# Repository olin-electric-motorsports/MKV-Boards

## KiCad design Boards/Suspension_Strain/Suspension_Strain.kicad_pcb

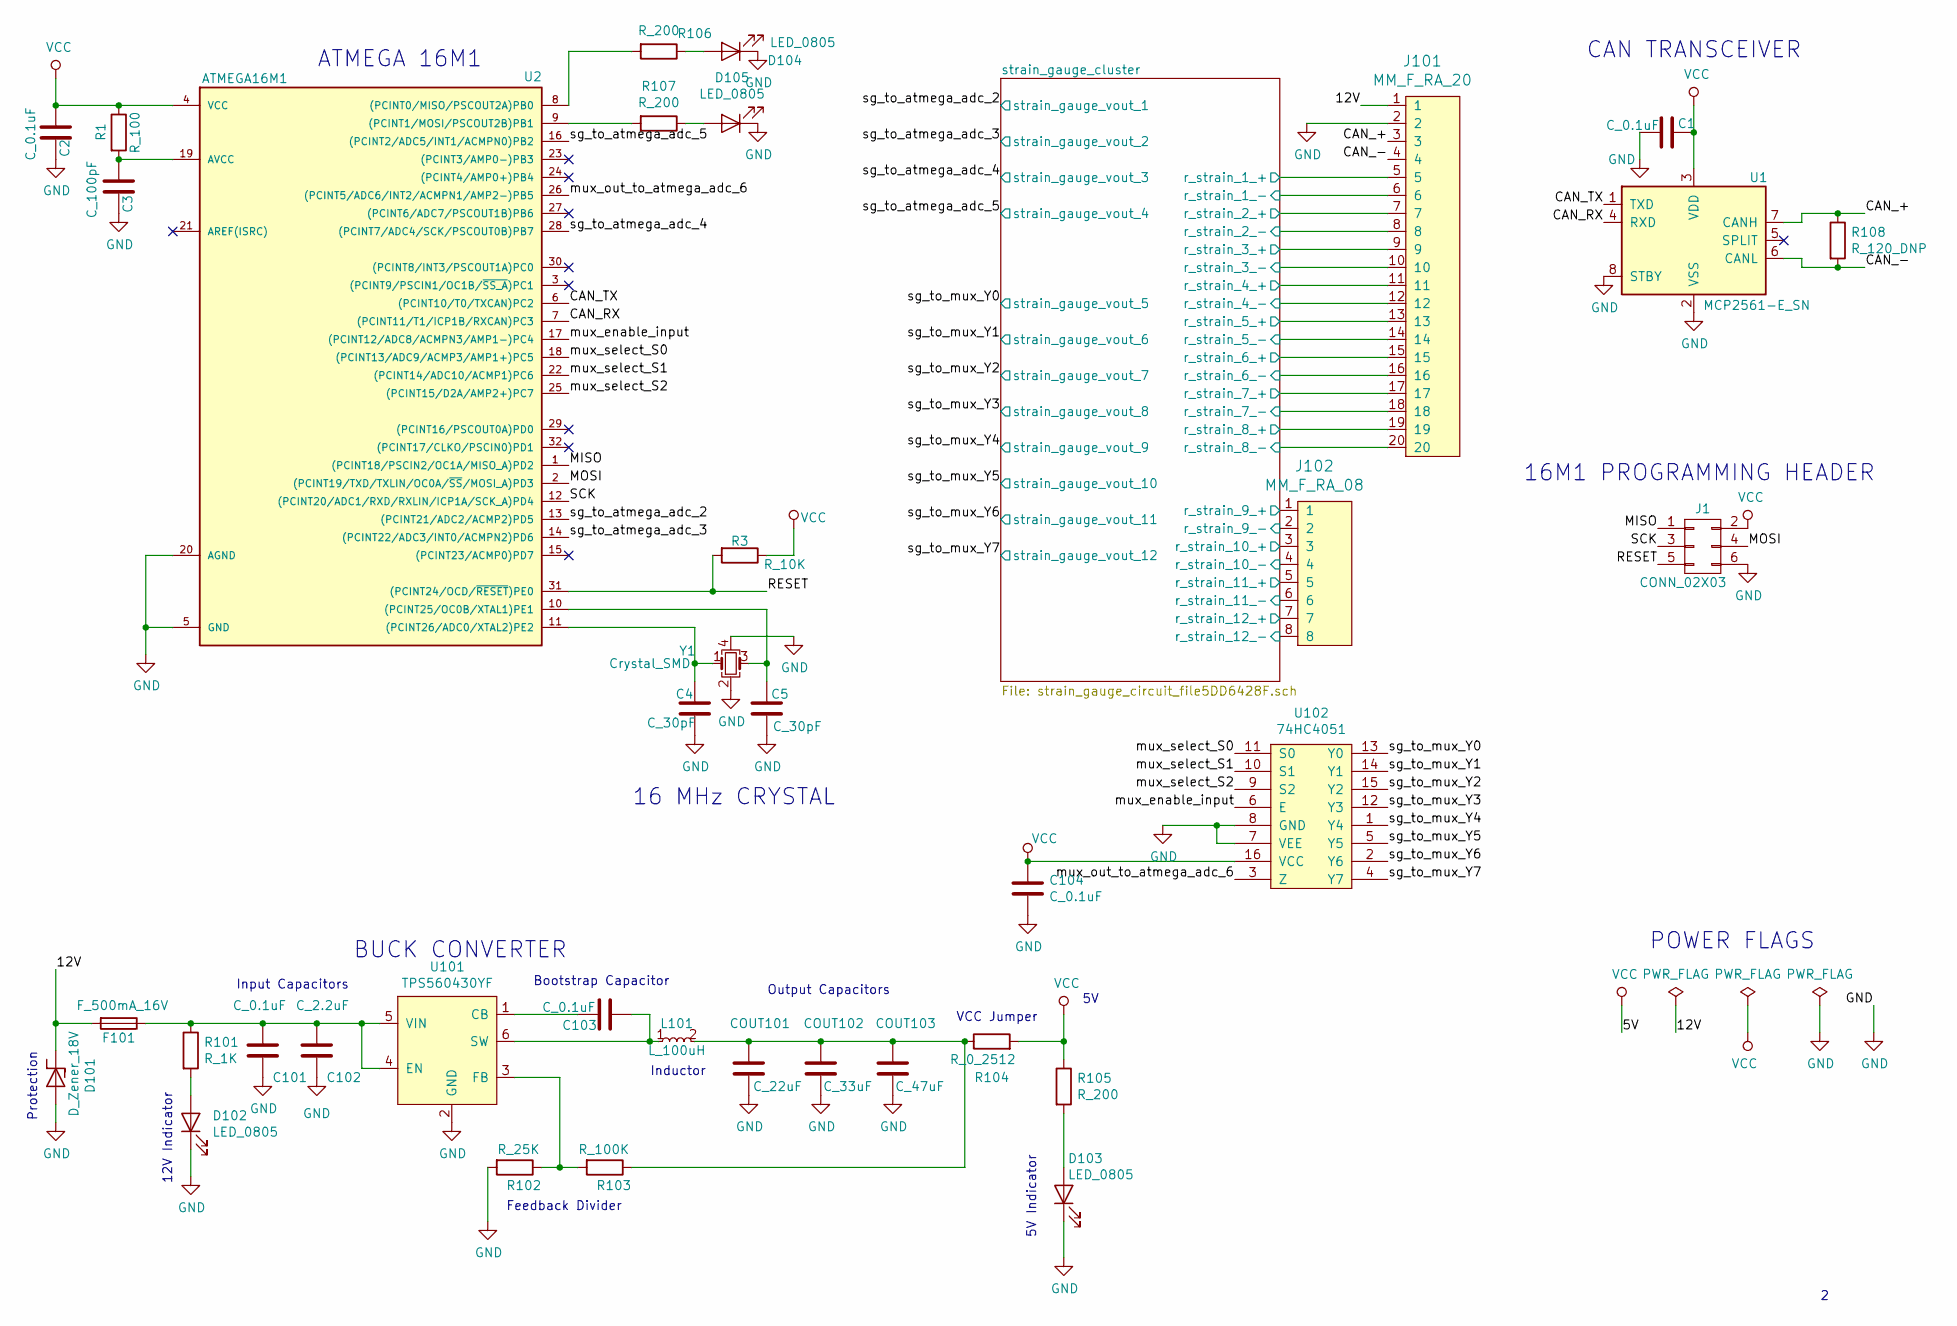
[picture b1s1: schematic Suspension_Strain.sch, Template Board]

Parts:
C1, C2, C101, C103, C104: C_0.1uF; C_0805_OEM; MPN 478-3352-1-ND
C3: C_100pF; C_0805_OEM; MPN 732-7852-1-ND
C4, C5: C_30pF; C_0805_OEM; MPN 1276-1130-1-ND
C102: C_2.2uF; C_0603_1608Metric; MPN 311-1451-1-ND
COUT101: C_22uF; C_1206_OEM; MPN 445-11693-1-ND
COUT102: C_33uF; C_1812_OEM; MPN 445-3924-1-ND
COUT103: C_47uF; C_0805_OEM; MPN 1276-6467-1-ND
D101: D_Zener_18V; DO-214AA; MPN SMBJ5355B-TPMSCT-ND
D102, D103, D104, D105: LED_0805; LED_0805_OEM; MPN 475-1410-1-ND
F101: F_500mA_16V; Fuse_1210; MPN 507-1786-1-ND
J1: CONN_02X03; Pin_Header_Straight_2x03; MPN 609-3234-ND
J101: MM_F_RA_20; micromatch_female_ra_20; MPN 2-338070-0
J102: MM_F_RA_08; micromatch_female_ra_8; MPN 338070-8
L101: L_100uH; L_100uH_OEM; MPN 445-15759-1-ND
R1: R_100; R_0805_OEM; MPN RNCP0805FTD100RCT-ND
R3: R_10K; R_0805_OEM; MPN CRS0805-FX-1002ELFCT-ND
R101: R_1K; R_0805_OEM; MPN RNCP0805FTD1K00CT-ND
R102: R_25K; R_0805_OEM; Digi-key Part Number CPF-A-0805B25KE
R103: R_100K; R_0805_OEM; MPN P100KCCT-ND
R104: R_0_2512; R_2512_OEM; MPN A121322CT-ND
R105, R106, R107: R_200; R_0805_OEM; MPN RMCF0805JT200RCT-ND
R108: R_120_DNP; R_0805_OEM; MPN 667-ERJ-6ENF1200V
U1: MCP2561-E_SN; SOIC-8_3.9x4.9mm_Pitch1.27mm_OEM; MPN MCP2561-E/SN-ND
U2: ATMEGA16M1; TQFP-32_7x7mm_Pitch0.8mm; MPN ATMEGA16M1-AU-ND
U101: TPS560430YF; SOT-23-6_Handsoldering; MPN TPS560430YFDBVR
U102: 74HC4051; TSSOP-16-OEM; MPN 1727-1033-1-ND
Y1: Crystal_SMD; Crystal_SMD_FA238; MPN 887-1125-1-ND

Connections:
/12V: D101.1 (K), F101.2, J101.1
/CAN_+: J101.3, R108.1, U1.7 (CANH)
/CAN_-: J101.4, R108.2, U1.6 (CANL)
/CAN_RX: U1.4 (RXD), U2.7 ((PCINT11/T1/ICP1B/RXCAN)PC3)
/CAN_TX: U1.1 (TXD), U2.6 ((PCINT10/T0/TXCAN)PC2)
/MISO: J1.1, U2.1 ((PCINT18/PSCIN2/OC1A/MISO_A)PD2)
/MOSI: J1.4, U2.2 ((PCINT19/TXD/TXLIN/OC0A/~SS~/MOSI_A)PD3)
/RESET: J1.5, R3.2, U2.31 ((PCINT24/OCD/~RESET~)PE0)
/SCK: J1.3, U2.12 ((PCINT20/ADC1/RXD/RXLIN/ICP1A/SCK_A)PD4)
/mux_enable_input: U2.17 ((PCINT12/ADC8/ACMPN3/AMP1-)PC4), U102.6 (E)
/mux_out_to_atmega_adc_6: U2.26 ((PCINT5/ADC6/INT2/ACMPN1/AMP2-)PB5), U102.3 (Z)
/mux_select_S0: U2.18 ((PCINT13/ADC9/ACMP3/AMP1+)PC5), U102.11 (S0)
/mux_select_S1: U2.22 ((PCINT14/ADC10/ACMP1)PC6), U102.10 (S1)
/mux_select_S2: U2.25 ((PCINT15/D2A/AMP2+)PC7), U102.9 (S2)
/sg_to_atmega_adc_2: U2.13 ((PCINT21/ADC2/ACMP2)PD5); also elsewhere on the board
/sg_to_atmega_adc_3: U2.14 ((PCINT22/ADC3/INT0/ACMPN2)PD6); also elsewhere on the board
/sg_to_atmega_adc_4: U2.28 ((PCINT7/ADC4/SCK/PSCOUT0B)PB7); also elsewhere on the board
/sg_to_atmega_adc_5: U2.16 ((PCINT2/ADC5/INT1/ACMPN0)PB2); also elsewhere on the board
/sg_to_mux_Y0: U102.13 (Y0); also elsewhere on the board
/sg_to_mux_Y1: U102.14 (Y1); also elsewhere on the board
/sg_to_mux_Y2: U102.15 (Y2); also elsewhere on the board
/sg_to_mux_Y3: U102.12 (Y3); also elsewhere on the board
/sg_to_mux_Y4: U102.1 (Y4); also elsewhere on the board
/sg_to_mux_Y5: U102.5 (Y5); also elsewhere on the board
/sg_to_mux_Y6: U102.2 (Y6); also elsewhere on the board
/sg_to_mux_Y7: U102.4 (Y7); also elsewhere on the board
/strain_gauge_cluster/r_strain_1_+: J101.5; also elsewhere on the board
/strain_gauge_cluster/r_strain_2_+: J101.7; also elsewhere on the board
/strain_gauge_cluster/r_strain_3_+: J101.9; also elsewhere on the board
/strain_gauge_cluster/r_strain_4_+: J101.11; also elsewhere on the board
/strain_gauge_cluster/r_strain_5_+: J101.13; also elsewhere on the board
/strain_gauge_cluster/r_strain_6_+: J101.15; also elsewhere on the board
/strain_gauge_cluster/r_strain_7_+: J101.17; also elsewhere on the board
/strain_gauge_cluster/r_strain_8_+: J101.19; also elsewhere on the board
/strain_gauge_cluster/r_strain_9_+: J102.1; also elsewhere on the board
/strain_gauge_cluster/r_strain_10_+: J102.3; also elsewhere on the board
/strain_gauge_cluster/r_strain_11_+: J102.5; also elsewhere on the board
/strain_gauge_cluster/r_strain_12_+: J102.7; also elsewhere on the board
GND: C1.2, C2.2, C3.2, C4.2, C5.2, C101.2, C102.2, C104.2, COUT101.2, COUT102.2, COUT103.2, D101.2 (A), D102.1 (K), D103.1 (K), D104.1 (K), D105.1 (K), J1.6, J101.2, J101.6, J101.8, J101.10, J101.12, J101.14, J101.16, J101.18, J101.20, J102.2, J102.4, J102.6, J102.8, R102.2, U1.2 (VSS), U1.8 (STBY), U2.5 (GND), U2.20 (AGND), U101.2 (GND), U102.7 (VEE), U102.8 (GND), Y1.2, Y1.4; also elsewhere on the board
unnamed: C3.1, R1.2, U2.19 (AVCC)
unnamed: C4.1, U2.11 ((PCINT26/ADC0/XTAL2)PE2), Y1.1
unnamed: C5.1, U2.10 ((PCINT25/OC0B/XTAL1)PE1), Y1.3
unnamed: C101.1, C102.1, F101.1, R101.1, U101.4 (EN), U101.5 (VIN)
unnamed: C103.1, U101.1 (CB)
unnamed: C103.2, L101.1, U101.6 (SW)
unnamed: COUT101.1, COUT102.1, COUT103.1, L101.2, R103.1, R104.1
unnamed: D102.2 (A), R101.2
unnamed: D103.2 (A), R105.2
unnamed: D104.2 (A), R106.1
unnamed: D105.2 (A), R107.1
unnamed: R102.1, R103.2, U101.3 (FB)
unnamed: R106.2, U2.8 ((PCINT0/MISO/PSCOUT2A)PB0)
unnamed: R107.2, U2.9 ((PCINT1/MOSI/PSCOUT2B)PB1)
VCC: C1.1, C2.1, C104.1, J1.2, R1.1, R3.1, R104.2, R105.1, U1.3 (VDD), U2.4 (VCC), U102.16 (VCC); also elsewhere on the board

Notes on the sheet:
Input Capacitors
12V Indicator
Protection
BUCK CONVERTER
Feedback Divider
Inductor
Bootstrap Capacitor
VCC Jumper
5V Indicator
CAN TRANSCEIVER
16 MHz CRYSTAL
POWER FLAGS
16M1 PROGRAMMING HEADER
ATMEGA 16M1
Output Capacitors

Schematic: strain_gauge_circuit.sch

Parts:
C401: C_0.1uF; C_0805_OEM; MPN 478-3352-1-ND
R101, R102, R103, R104, R105: R_120; R_0805_OEM; MPN 667-ERJ-6ENF1200V
R106, R407: R_4.99K; R_0805_OEM; MPN RNCP0805FTD4K99CT-ND
U101: MCP6001T-I-LT; SOT-353_SC-70-5; MPN MCP6001T-I/LTCT-ND

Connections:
/sg_to_atmega_adc_2: R407.1; also elsewhere on the board
GND: C401.2; also elsewhere on the board
unnamed 58: R407.2; also elsewhere on the board
VCC: C401.1; also elsewhere on the board

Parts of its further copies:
C301, C501, C601, C701, C801, C901, C1001, C1101, C1201, C1301, C1401: C_0.1uF; C_0805_OEM; MPN 478-3352-1-ND
R301, R302, R303, R304, R305, R401, R402, R403, R404, R405, R501, R502, R503, R504, R505, R601, R602, R603, R604, R605, R701, R702, R703, R704, R705, R801, R802, R803, R804, R805, R901, R902, R903, R904, R905, R1001, R1002, R1003, R1004, R1005, R1101, R1102, R1103, R1104, R1105, R1201, R1202, R1203, R1204, R1205, R1301, R1302, R1303, R1304, R1305, R1401, R1402, R1403, R1404, R1405: R_120; R_0805_OEM; MPN 667-ERJ-6ENF1200V
R306, R307, R406, R506, R507, R606, R607, R706, R707, R806, R807, R906, R907, R1006, R1007, R1106, R1107, R1206, R1207, R1306, R1307, R1406, R1407: R_4.99K; R_0805_OEM; MPN RNCP0805FTD4K99CT-ND
U301, U401, U501, U601, U701, U801, U901, U1001, U1101, U1201, U1301, U1401: MCP6001T-I-LT; SOT-353_SC-70-5; MPN MCP6001T-I/LTCT-ND

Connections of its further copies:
/sg_to_atmega_adc_2: U401.1; also elsewhere on the board
/sg_to_atmega_adc_3: R307.1, U301.1; also elsewhere on the board
/sg_to_atmega_adc_4: R507.1, U501.1; also elsewhere on the board
/sg_to_atmega_adc_5: R607.1, U601.1; also elsewhere on the board
/sg_to_mux_Y0: R707.1, U701.1; also elsewhere on the board
/sg_to_mux_Y1: R807.1, U801.1; also elsewhere on the board
/sg_to_mux_Y2: R907.1, U901.1; also elsewhere on the board
/sg_to_mux_Y3: R1007.1, U1001.1; also elsewhere on the board
/sg_to_mux_Y4: R1107.1, U1101.1; also elsewhere on the board
/sg_to_mux_Y5: R1207.1, U1201.1; also elsewhere on the board
/sg_to_mux_Y6: R1307.1, U1301.1; also elsewhere on the board
/sg_to_mux_Y7: R1407.1, U1401.1; also elsewhere on the board
/strain_gauge_cluster/r_strain_1_+: R401.1, R404.2; also elsewhere on the board
/strain_gauge_cluster/r_strain_2_+: R301.1, R304.2; also elsewhere on the board
/strain_gauge_cluster/r_strain_3_+: R501.1, R504.2; also elsewhere on the board
/strain_gauge_cluster/r_strain_4_+: R601.1, R604.2; also elsewhere on the board
/strain_gauge_cluster/r_strain_5_+: R701.1, R704.2; also elsewhere on the board
/strain_gauge_cluster/r_strain_6_+: R801.1, R804.2; also elsewhere on the board
/strain_gauge_cluster/r_strain_7_+: R901.1, R904.2; also elsewhere on the board
/strain_gauge_cluster/r_strain_8_+: R1001.1, R1004.2; also elsewhere on the board
/strain_gauge_cluster/r_strain_9_+: R1101.1, R1104.2; also elsewhere on the board
/strain_gauge_cluster/r_strain_10_+: R1201.1, R1204.2; also elsewhere on the board
/strain_gauge_cluster/r_strain_11_+: R1301.1, R1304.2; also elsewhere on the board
/strain_gauge_cluster/r_strain_12_+: R1401.1, R1404.2; also elsewhere on the board
GND: C301.2, C501.2, C601.2, C701.2, C801.2, C901.2, C1001.2, C1101.2, C1201.2, C1301.2, C1401.2, R303.1, R306.2, R403.1, R406.2, R503.1, R506.2, R603.1, R606.2, R703.1, R706.2, R803.1, R806.2, R903.1, R906.2, R1003.1, R1006.2, R1103.1, R1106.2, R1203.1, R1206.2, R1303.1, R1306.2, R1403.1, R1406.2, U301.2, U401.2, U501.2, U601.2, U701.2, U801.2, U901.2, U1001.2, U1101.2, U1201.2, U1301.2, U1401.2; also elsewhere on the board
unnamed: R302.1, R303.2, R305.2
unnamed: R304.1, R306.1, U301.3
unnamed: R305.1, R307.2, U301.4
unnamed: R402.1, R403.2, R405.2
unnamed: R404.1, R406.1, U401.3
unnamed 58: R405.1, U401.4; also elsewhere on the board
unnamed: R502.1, R503.2, R505.2
unnamed: R504.1, R506.1, U501.3
unnamed: R505.1, R507.2, U501.4
unnamed: R602.1, R603.2, R605.2
unnamed: R604.1, R606.1, U601.3
unnamed: R605.1, R607.2, U601.4
unnamed: R702.1, R703.2, R705.2
unnamed: R704.1, R706.1, U701.3
unnamed: R705.1, R707.2, U701.4
unnamed: R802.1, R803.2, R805.2
unnamed: R804.1, R806.1, U801.3
unnamed: R805.1, R807.2, U801.4
unnamed: R902.1, R903.2, R905.2
unnamed: R904.1, R906.1, U901.3
unnamed: R905.1, R907.2, U901.4
unnamed: R1002.1, R1003.2, R1005.2
unnamed: R1004.1, R1006.1, U1001.3
unnamed: R1005.1, R1007.2, U1001.4
unnamed: R1102.1, R1103.2, R1105.2
unnamed: R1104.1, R1106.1, U1101.3
unnamed: R1105.1, R1107.2, U1101.4
unnamed: R1202.1, R1203.2, R1205.2
unnamed: R1204.1, R1206.1, U1201.3
unnamed: R1205.1, R1207.2, U1201.4
unnamed: R1302.1, R1303.2, R1305.2
unnamed: R1304.1, R1306.1, U1301.3
unnamed: R1305.1, R1307.2, U1301.4
unnamed: R1402.1, R1403.2, R1405.2
unnamed: R1404.1, R1406.1, U1401.3
unnamed: R1405.1, R1407.2, U1401.4
VCC: C301.1, C501.1, C601.1, C701.1, C801.1, C901.1, C1001.1, C1101.1, C1201.1, C1301.1, C1401.1, R301.2, R302.2, R401.2, R402.2, R501.2, R502.2, R601.2, R602.2, R701.2, R702.2, R801.2, R802.2, R901.2, R902.2, R1001.2, R1002.2, R1101.2, R1102.2, R1201.2, R1202.2, R1301.2, R1302.2, R1401.2, R1402.2, U301.5, U401.5, U501.5, U601.5, U701.5, U801.5, U901.5, U1001.5, U1101.5, U1201.5, U1301.5, U1401.5; also elsewhere on the board

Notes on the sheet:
Strain Gauge Circuit

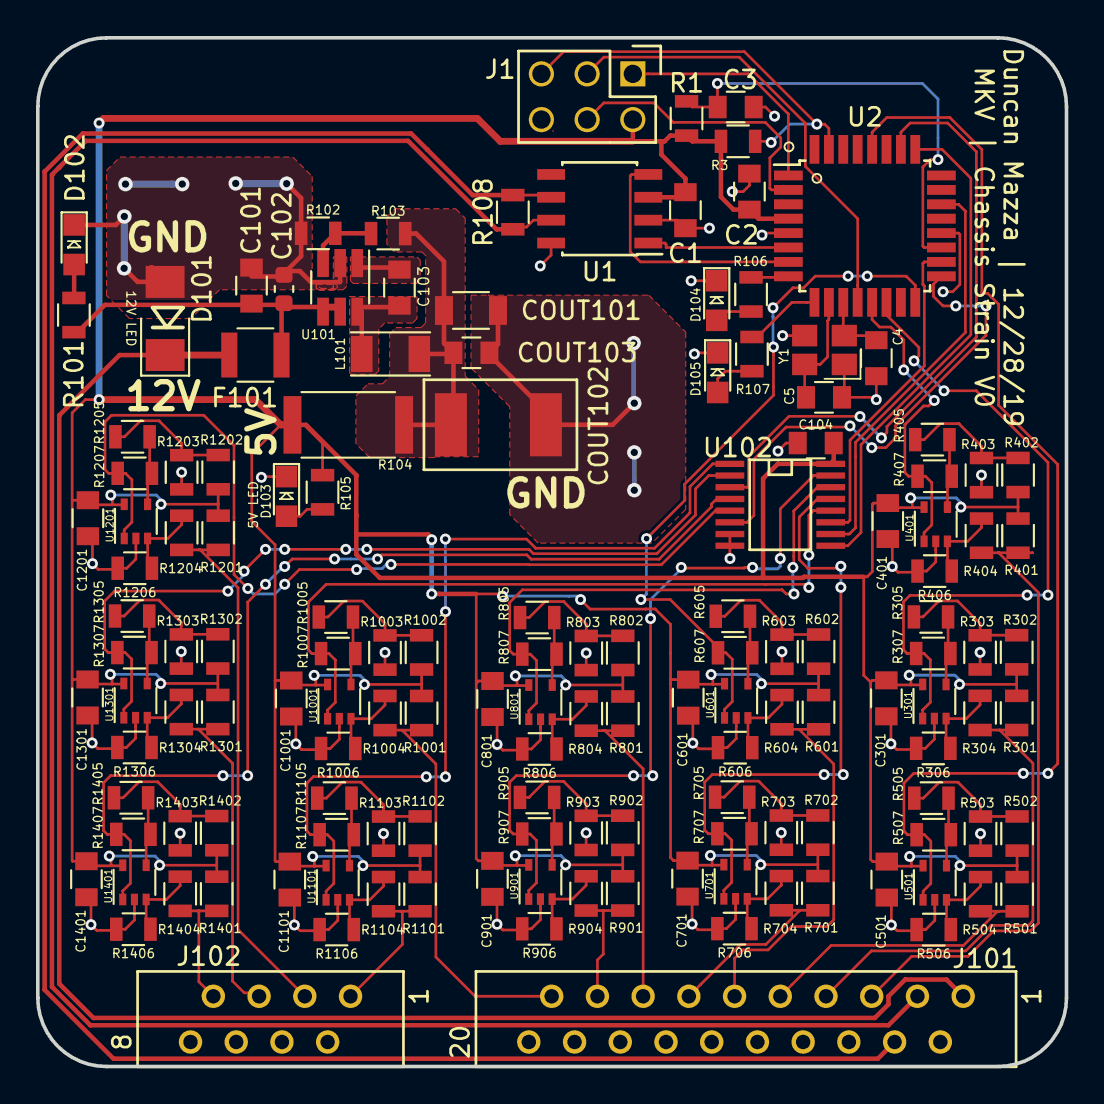
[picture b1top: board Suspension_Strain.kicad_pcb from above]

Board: 2 copper layers, 57.2 x 57.2 mm, 145 parts (0 on the bottom side), 90 nets.

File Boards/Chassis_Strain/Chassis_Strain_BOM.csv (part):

Reference, Value, Footprint, Datasheet, MFN, MPN, PurchasingLink, Digi-key Part Number, Link, Purchasing Link
"C102","C_2.2uF","footprints:C_0603_1608Metric","http://www.yageo.com/documents/recent/UPY-GPHC_X5R_4V-to-50V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","DK","311-1451-1-ND","https://www.digikey.com/product-detail/en/yageo/CC0603KRX5R6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","","",""
"C101","C_0.1uF","footprints:C_0805_OEM","http://datasheets.avx.com/X7RDielectric.pdf","DK","478-3352-1-ND","https://www.digikey.com/products/en?keywords=478-3352-1-ND","","",""
"R103","R_100K","footprints:R_0805_OEM","https://industrial.panasonic.com/cdbs/www-data/pdf/RDA0000/A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","DK","P100KCCT-ND","https://www.digikey.com/product-detail/en/panasonic-electron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","","",""
"C103","C_0.1uF","footprints:C_0805_OEM","http://datasheets.avx.com/X7RDielectric.pdf","DK","478-3352-1-ND","https://www.digikey.com/products/en?keywords=478-3352-1-ND","","",""
"COUT101","C_22uF","footprints:C_1206_OEM","https://product.tdk.com/info/en/catalog/datasheets/mlcc_comm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","DK","445-11693-1-ND","https://www.digikey.com/product-detail/en/tdk-corporation/C3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","","",""
"COUT103","C_47uF","footprints:C_0805_OEM","http://www.samsungsem.com/kr/support/product-search/mlcc/__i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","DK","1276-6467-1-ND","https://www.digikey.com/product-detail/en/samsung-electro-me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","","",""
"COUT102","C_33uF","footprints:C_1812_OEM","https://product.tdk.com/info/en/catalog/datasheets/mlcc_comm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","C4532X7R1C336M250KC","445-3924-1-ND","https://www.digikey.com/product-detail/en/tdk-corporation/C4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","","",""
"R102","R_25K","footprints:R_0805_OEM","https://www.te.com/commerce/DocumentDelivery/DDEController?A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","A124124CT-ND","","https://www.digikey.com/product-detail/en/te-connectivity-pa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","CPF-A-0805B25KE","",""
"F101","F_500mA_16V","footprints:Fuse_1210","https://belfuse.com/resources/CircuitProtection/datasheets/0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","DK","507-1786-1-ND","https://www.digikey.com/product-detail/en/bel-fuse-inc/0ZCH0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","","",""
"R104","R_0_2512","footprints:R_2512_OEM","http://www.te.com/commerce/DocumentDelivery/DDEController?Ac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","DK","A121322CT-ND","https://www.digikey.com/products/en?keywords=A121322CT-ND","","",""
"D103","LED_0805","footprints:LED_0805_OEM","http://www.osram-os.com/Graphics/XPic9/00078860_0.pdf","DK","475-1410-1-ND","https://www.digikey.com/products/en?keywords=475-1410-1-ND","","",""
"R105","R_200","footprints:R_0805_OEM","https://www.seielect.com/Catalog/SEI-RMCF_RMCP.pdf","DK","RMCF0805JT200RCT-ND","https://www.digikey.com/products/en?keywords=RMCF0805JT200RCT-ND","","",""
"D101","D_Zener_18V","footprints:DO-214AA","http://www.mccsemi.com/up_pdf/SMBJ5338B-SMBJ5388B(SMB).pdf","DK","SMBJ5355B-TPMSCT-ND","https://www.digikey.com/products/en?keywords=SMBJ5355B-TPMSCT-ND","","",""
"D102","LED_0805","footprints:LED_0805_OEM","http://www.osram-os.com/Graphics/XPic9/00078860_0.pdf","DK","475-1410-1-ND","https://www.digikey.com/products/en?keywords=475-1410-1-ND","","",""
"L101","L_100uH","footprints:L_100uH_OEM","https://product.tdk.com/info/en/catalog/datasheets/inductor_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","Digikey","445-15759-1-ND","","","https://www.digikey.com/product-detail/en/tdk-corporation/NL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",""
"R1","R_100","footprints:R_0805_OEM","https://www.seielect.com/Catalog/SEI-rncp.pdf","DK","RNCP0805FTD100RCT-ND","https://www.digikey.com/products/en?keywords=RNCP0805FTD100RCT-ND","","",""
"C3","C_100pF","footprints:C_0805_OEM","https://katalog.we-online.de/pbs/datasheet/885012007057.pdf","DK","732-7852-1-ND","https://www.digikey.com/product-detail/en/wurth-electronics-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","","",""
"Y1","Crystal_SMD","footprints:Crystal_SMD_FA238","http://www.txccorp.com/download/products/quartz_crystals/201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","DK","887-1125-1-ND","https://www.digikey.com/product-detail/en/txc-corporation/7M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","","",""
"C4","C_30pF","footprints:C_0805_OEM","https://media.digikey.com/pdf/Data%20Sheets/Samsung%20PDFs/C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","DK","1276-1130-1-ND","https://www.digikey.com/product-detail/en/samsung-electro-me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","","",""
"C5","C_30pF","footprints:C_0805_OEM","https://media.digikey.com/pdf/Data%20Sheets/Samsung%20PDFs/C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","DK","1276-1130-1-ND","https://www.digikey.com/product-detail/en/samsung-electro-me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","","",""
"R3","R_10K","footprints:R_0805_OEM","http://www.bourns.com/data/global/pdfs/CRS.pdf","DK","CRS0805-FX-1002ELFCT-ND","https://www.digikey.com/products/en?keywords=CRS0805-FX-1002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","","",""
"U1","MCP2561-E_SN","footprints:SOIC-8_3.9x4.9mm_Pitch1.27mm_OEM","http://www.microchip.com/mymicrochip/filehandler.aspx?ddocna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","DK","MCP2561-E/SN-ND","https://www.digikey.com/products/en?keywords=mcp2561-e%2Fsn","","",""
"C1","C_0.1uF","footprints:C_0805_OEM","http://datasheets.avx.com/X7RDielectric.pdf","DK","478-3352-1-ND","https://www.digikey.com/products/en?keywords=478-3352-1-ND","","",""
"J1","CONN_02X03","footprints:Pin_Header_Straight_2x03","http://portal.fciconnect.com/Comergent//fci/drawing/67996.pdf","DK","609-3234-ND","https://www.digikey.com/product-detail/en/amphenol-fci/67997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","","",""
"C2","C_0.1uF","footprints:C_0805_OEM","http://datasheets.avx.com/X7RDielectric.pdf","DK","478-3352-1-ND","https://www.digikey.com/products/en?keywords=478-3352-1-ND","","",""
"U101","TPS560430YF","Package_TO_SOT_SMD:SOT-23-6_Handsoldering","http://www.ti.com/lit/ds/symlink/tps560430.pdf","TPS560430YFDBVR-ND","TPS560430YFDBVR","","","","https://www.digikey.com/product-detail/en/texas-instruments/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"
"U2","ATMEGA16M1","footprints:TQFP-32_7x7mm_Pitch0.8mm","http://ww1.microchip.com/downloads/en/DeviceDoc/Atmel-8209-8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","DK","ATMEGA16M1-AU-ND","https://www.digikey.com/product-detail/en/atmel/ATMEGA16M1-A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","","",""
"J101","MM_F_RA_20","footprints:micromatch_female_ra_20","http://www.te.com/commerce/DocumentDelivery/DDEController?Ac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","TE","2-338070-0","http://www.te.com/usa-en/product-2-338070-0.html","","",""
"J102","MM_F_RA_08","footprints:micromatch_female_ra_8","http://www.te.com/commerce/DocumentDelivery/DDEController?Ac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","TE","338070-8","http://www.te.com/usa-en/product-338070-8.html","","",""
"R108","R_120_DNP","footprints:R_0805_OEM","https://www.mouser.com/datasheet/2/315/AOA0000C304-1149620.pdf","DK","667-ERJ-6ENF1200V","https://www.mouser.com/ProductDetail/Panasonic-Industrial-De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","","",""
"U102","74HC4051","footprints:TSSOP-16-OEM","https://assets.nexperia.com/documents/data-sheet/74HC_HCT405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","DK","1727-1033-1-ND","https://www.digikey.com/product-detail/en/nexperia-usa-inc/7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","","",""
"R101","R_1K","footprints:R_0805_OEM","https://www.seielect.com/Catalog/SEI-rncp.pdf","DK","RNCP0805FTD1K00CT-ND","https://www.digikey.com/products/en?keywords=RNCP0805FTD1K00CT-ND","","",""
"D104","LED_0805","footprints:LED_0805_OEM","http://www.osram-os.com/Graphics/XPic9/00078860_0.pdf","DK","475-1410-1-ND","https://www.digikey.com/products/en?keywords=475-1410-1-ND","","",""
"R106","R_200","footprints:R_0805_OEM","https://www.seielect.com/Catalog/SEI-RMCF_RMCP.pdf","DK","RMCF0805JT200RCT-ND","https://www.digikey.com/products/en?keywords=RMCF0805JT200RCT-ND","","",""
"D105","LED_0805","footprints:LED_0805_OEM","http://www.osram-os.com/Graphics/XPic9/00078860_0.pdf","DK","475-1410-1-ND","https://www.digikey.com/products/en?keywords=475-1410-1-ND","","",""
"R107","R_200","footprints:R_0805_OEM","https://www.seielect.com/Catalog/SEI-RMCF_RMCP.pdf","DK","RMCF0805JT200RCT-ND","https://www.digikey.com/products/en?keywords=RMCF0805JT200RCT-ND","","",""
"C104","C_0.1uF","footprints:C_0805_OEM","http://datasheets.avx.com/X7RDielectric.pdf","DK","478-3352-1-ND","https://www.digikey.com/products/en?keywords=478-3352-1-ND","","",""
"R306","R_4.99K","footprints:R_0805_OEM","https://www.digikey.com/product-detail/en/yageo/RC0402FR-074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","DK","RNCP0805FTD4K99CT-ND ","https://www.digikey.com/product-detail/en/stackpole-electron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","","",""
"R305","R_120","footprints:R_0805_OEM","https://www.mouser.com/datasheet/2/315/AOA0000C304-1149620.pdf","DK","667-ERJ-6ENF1200V","https://www.mouser.com/ProductDetail/Panasonic-Industrial-De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","","",""
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
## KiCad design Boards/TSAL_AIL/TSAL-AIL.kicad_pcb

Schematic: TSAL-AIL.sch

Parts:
C1: C_10uF; C_0805_OEM; MPN 1276-1052-1-ND
C2: C_0.1uF; C_0805_OEM; MPN 478-3352-1-ND
C3, C4: C_1uF; C_0805_OEM; MPN 1276-2887-1-ND
D1: LED_0805; LED_0805_OEM; MPN 475-1410-1-ND
F1: F_21mA_420V; MPN 495-75309-ND
J1: Ultrafit_4_RA; MPN WM11574-ND
J2: NanoFit_2; NanoFit_Molex_1x02x2.50mm_Angled_OEM; MPN WM14972-ND
J3: MM_F_RA_06; micromatch_female_ra_6; MPN 338070-6
Q1, Q2: SSM3K333R; SOT-23F; MPN SSM3K333RLFCT-ND
R1, R4, R6, R7: R_270K; R_0805_OEM; MPN P270KDACT-ND
R2, R10, R11: R_1K; R_0805_OEM; MPN RNCP0805FTD1K00CT-ND
R3: R_137; R_0805_OEM
R5, R13, R14: R_10K; R_0805_OEM; MPN CRS0805-FX-1002ELFCT-ND
R8: R_3K; R_0805_OEM; MPN RMCF0805FT3K00CT-ND
R9: R_1.43K; R_0805_OEM; MPN A103351CT-ND
R12: R_499; R_0805_OEM; MPN P499CCT-ND
U1: MCP6001; SOT-23-5; MPN MCP6001T-I/OTCT-ND
U2: LR8K4-G; TO-252-2; MPN 689-LR8K4-G
U3: CPC1025NTR; DIP-5-6_W7.62mm
U4: BU4S11G2-TR; SSOP5; MPN BU4S11G2-TR

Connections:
/5V: C1.2, C2.2, C3.1, R2.2, R10.1, U1.5 (V+), U2.2
/AIL+: C1.1, C2.1, C3.2, J1.2, J1.4, J2.1, R3.2, R5.2, R8.1, R9.2, R11.2, U1.2 (V-), U3.2
/AIL-: J2.2
/GLV+: C4.2, J3.2, J3.3, J3.5, U3.4, U4.2 (in), U4.5 (VCC)
/NAND_Out: Q2.1 (G), R14.1, U4.4 (out)
/TS+: F1.2, J1.1, J1.3, R1.2
/TSAL_FLAG: Q1.1 (G), R13.1, U3.3, U4.1 (in)
/TSAL_GREEN-: J3.4, Q2.3 (D)
/TSAL_RED-: J3.6, Q1.3 (D)
GND: C4.1, J3.1, Q1.2 (S), Q2.2 (S), R13.2, R14.2, U4.3 (GND)
unnamed: D1.1 (K), R11.1
unnamed: D1.2 (A), R9.1, R12.2, U1.1
unnamed: F1.1, U2.1
unnamed: R1.1, R4.2
unnamed: R2.1, R3.1, U1.4 (-)
unnamed: R4.1, R6.2
unnamed: R5.1, R7.1, U1.3 (+)
unnamed: R6.1, R7.2
unnamed: R8.2, R10.2, U2.3
unnamed: R12.1, U3.1

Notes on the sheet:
this is supposed to be R_137 but its not in the library?
RED TSAL
GREEN TSAL
Step Down
should this be TSAL_GREEN- ?

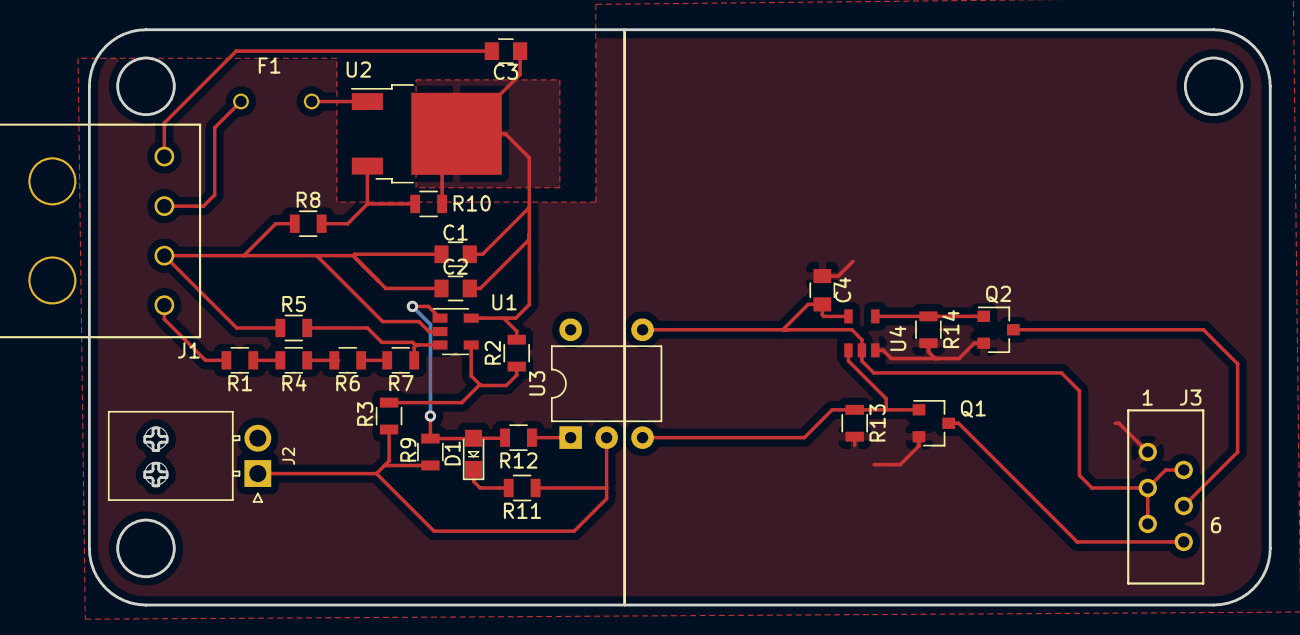
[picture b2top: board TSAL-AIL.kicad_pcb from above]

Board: 2 copper layers, 83.4 x 40.6 mm, 29 parts (0 on the bottom side), 19 nets.

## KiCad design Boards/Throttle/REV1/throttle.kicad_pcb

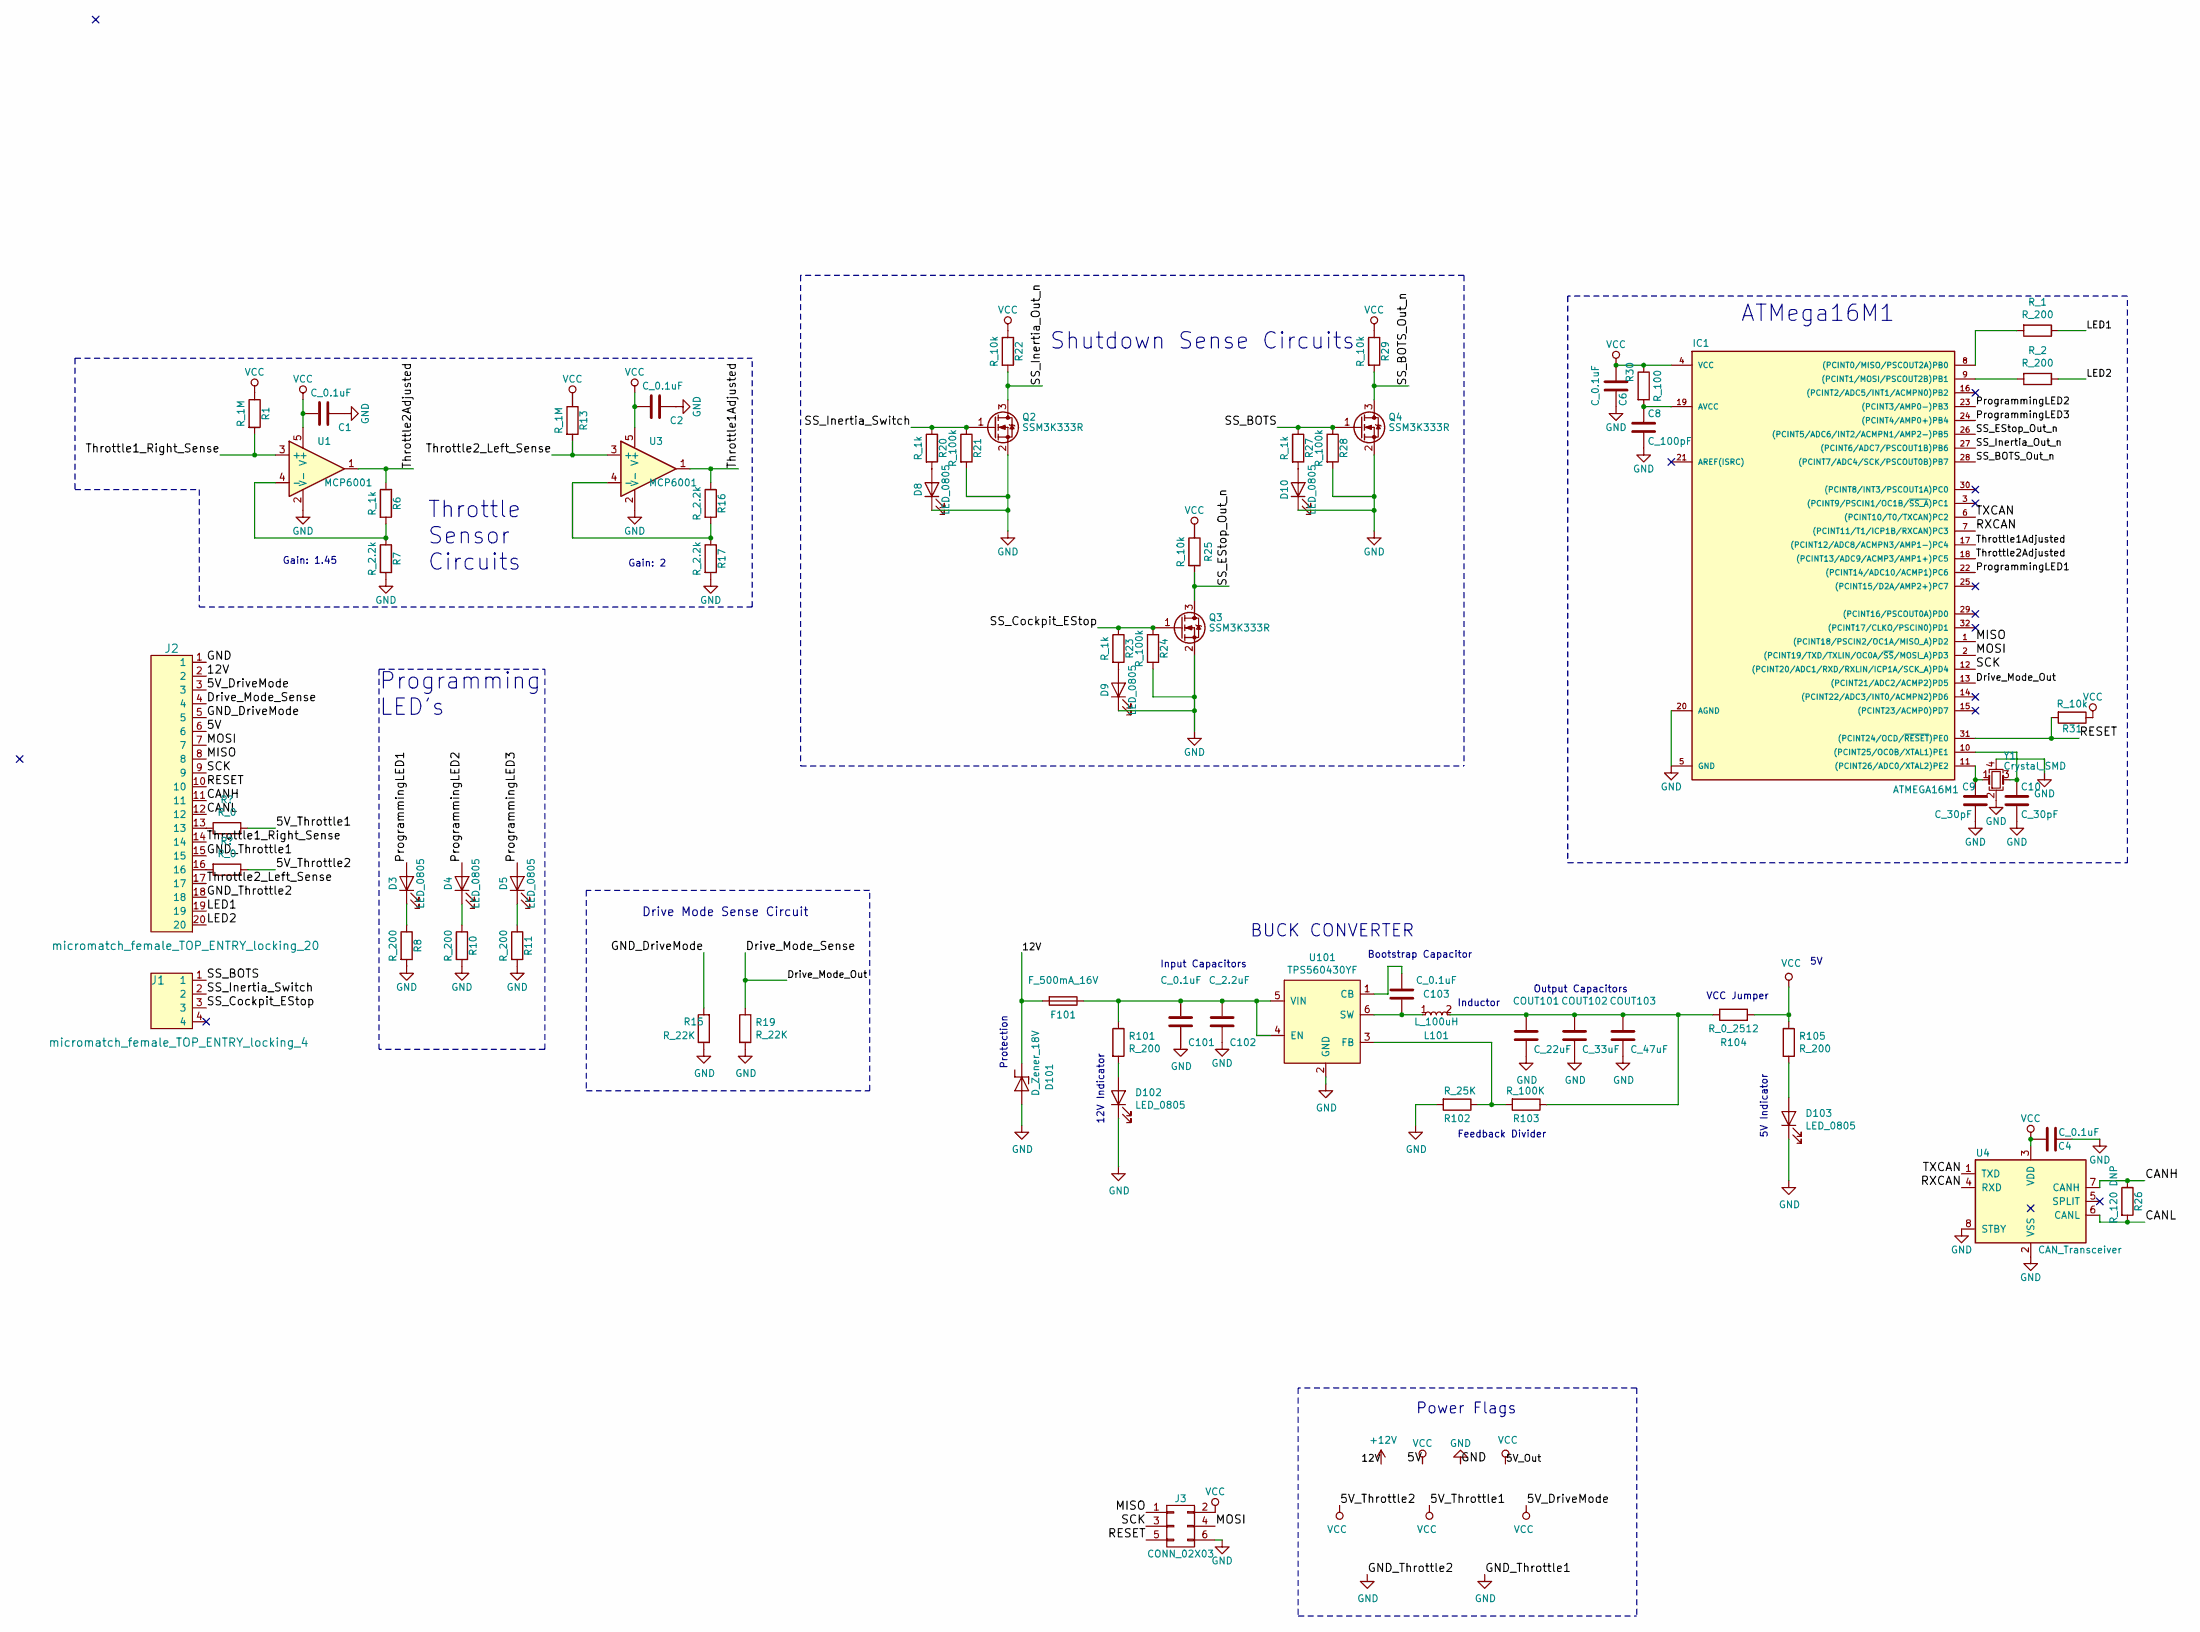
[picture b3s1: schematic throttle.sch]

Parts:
C1, C2, C4, C6, C101, C103: C_0.1uF; C_0805_OEM; MPN 478-3352-1-ND
C8: C_100pF; C_0805_OEM; MPN 732-7852-1-ND
C9, C10: C_30pF; C_0805_OEM; MPN 1276-1130-1-ND
C102: C_2.2uF; C_0603_1608Metric; MPN 311-1451-1-ND
COUT101: C_22uF; C_1206_OEM; MPN 445-11693-1-ND
COUT102: C_33uF; Fuse_1812; MPN 445-3924-1-ND
COUT103: C_47uF; C_0805_OEM; MPN 1276-6467-1-ND
D3, D4, D5, D8, D9, D10, D102, D103: LED_0805; LED_0805_OEM; MPN 475-1410-1-ND
D101: D_Zener_18V; DO-214AA; MPN SMBJ5355B-TPMSCT-ND
F101: F_500mA_16V; Fuse_1210; MPN 507-1786-1-ND
IC1: ATMEGA16M1; TQFP-32_7x7mm_Pitch0.8mm; MPN ATMEGA16M1-AU-ND
J1: micromatch_female_TOP_ENTRY_locking_4; micromatch_female_vert_4; MPN 338068-4
J2: micromatch_female_TOP_ENTRY_locking_20; micromatch_female_vert_20; MPN 2-338068-0
J3: CONN_02X03; Pin_Header_Straight_2x03; MPN 609-3234-ND
L101: L_100uH; MPN 445-15759-1-ND
Q2, Q3, Q4: SSM3K333R; SOT-23F; MPN SSM3K333RLFCT-ND
R1, R13: R_1M; R_0805_OEM; MPN RMCF0805JT1M00CT-ND
R6, R20, R23, R27: R_1k; R_0805_OEM; MPN RNCP0805FTD1K00CT-ND
R7, R16, R17: R_2.2k; R_0805_OEM; MPN RMCF0805FT2K20CT-ND
R8, R10, R11, R101, R105: R_200; R_0805_OEM; MPN RMCF0805JT200RCT-ND
R15, R19: R_22K; R_0805_OEM; MPN RMCF0805JT22K0CT-ND
R21, R24, R28: R_100k; R_0805_OEM; MPN P100KCCT-ND
R22, R25, R29, R31: R_10k; R_0805_OEM; MPN CRS0805-FX-1002ELFCT-ND
R26: R_120 DNP; R_0805_OEM; MPN RMCF0805JT200RCT-ND
R30: R_100; R_0805_OEM; MPN RNCP0805FTD100RCT-ND
R102: R_25K; R_0805_OEM; Digi-key Part Number CPF-A-0805B25KE
R103: R_100K; R_0805_OEM; MPN P100KCCT-ND
R104: R_0_2512; R_2512_OEM; MPN A121322CT-ND
R_1, R_2: R_200; R_0805_OEM; MPN RMCF0805JT200RCT-ND
U1, U3: MCP6001; SOT-23-5_OEM; MPN MCP6001T-I/OTCT-ND
U4: CAN_Transceiver; SOIC-8_3.9x4.9mm_Pitch1.27mm_OEM; MPN MCP2561-E/SN-ND
U101: TPS560430YF; SOT-23-6_Handsoldering; MPN TPS560430YFDBVR
Y1: Crystal_SMD; Crystal_SMD_FA238; MPN 887-1125-1-ND

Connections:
+12V: D101.1 (K), F101.2, J2.2
/CANH: J2.11, R26.1, U4.7 (CANH)
/CANL: J2.12, R26.2, U4.6 (CANL)
/Drive_Mode_Out: IC1.13 ((PCINT21/ADC2/ACMP2)PD5), J2.4, R19.1
/GND_DriveMode: J2.5, R15.2
/LED1: J2.19, R_1.1
/LED2: J2.20, R_2.1
/MISO: IC1.1 ((PCINT18/PSCIN2/OC1A/MISO_A)PD2), J2.8, J3.1
/MOSI: IC1.2 ((PCINT19/TXD/TXLIN/OC0A/~SS~/MOSI_A)PD3), J2.7, J3.4
/ProgrammingLED1: D3.2 (A), IC1.22 ((PCINT14/ADC10/ACMP1)PC6)
/ProgrammingLED2: D4.2 (A), IC1.23 ((PCINT3/AMP0-)PB3)
/ProgrammingLED3: D5.2 (A), IC1.24 ((PCINT4/AMP0+)PB4)
/RESET: IC1.31 ((PCINT24/OCD/~RESET~)PE0), J2.10, J3.5, R31.2
/RXCAN: IC1.7 ((PCINT11/T1/ICP1B/RXCAN)PC3), U4.4 (RXD)
/SCK: IC1.12 ((PCINT20/ADC1/RXD/RXLIN/ICP1A/SCK_A)PD4), J2.9, J3.3
/SS_BOTS: J1.1, Q4.1 (G), R27.1, R28.1
/SS_BOTS_Out_n: IC1.28 ((PCINT7/ADC4/SCK/PSCOUT0B)PB7), Q4.3 (D), R29.2
/SS_Cockpit_EStop: J1.3, Q3.1 (G), R23.1, R24.1
/SS_EStop_Out_n: IC1.26 ((PCINT5/ADC6/INT2/ACMPN1/AMP2-)PB5), Q3.3 (D), R25.2
/SS_Inertia_Out_n: IC1.27 ((PCINT6/ADC7/PSCOUT1B)PB6), Q2.3 (D), R22.2
/SS_Inertia_Switch: J1.2, Q2.1 (G), R20.1, R21.1
/TXCAN: IC1.6 ((PCINT10/T0/TXCAN)PC2), U4.1 (TXD)
/Throttle1Adjusted: IC1.17 ((PCINT12/ADC8/ACMPN3/AMP1-)PC4), R16.1, U3.1
/Throttle1_Right_Sense: J2.14, R1.2, U1.3 (+)
/Throttle2Adjusted: IC1.18 ((PCINT13/ADC9/ACMP3/AMP1+)PC5), R6.1, U1.1
/Throttle2_Left_Sense: J2.17, R13.2, U3.3 (+)
GND: C1.1, C2.1, C4.2, C6.2, C8.2, C9.2, C10.2, C101.2, C102.2, COUT101.2, COUT102.2, COUT103.2, D8.1 (K), D9.1 (K), D10.1 (K), D101.2 (A), D102.1 (K), D103.1 (K), IC1.5 (GND), IC1.20 (AGND), J2.1, J2.15, J2.18, J3.6, Q2.2 (S), Q3.2 (S), Q4.2 (S), R7.2, R8.2, R10.2, R11.2, R15.1, R17.2, R19.2, R21.2, R24.2, R28.2, R102.2, U1.2 (V-), U3.2 (V-), U4.2 (VSS), U4.8 (STBY), U101.2 (GND), Y1.2, Y1.4
unnamed: C8.1, IC1.19 (AVCC), R30.2
unnamed: C9.1, IC1.11 ((PCINT26/ADC0/XTAL2)PE2), Y1.1
unnamed: C10.1, IC1.10 ((PCINT25/OC0B/XTAL1)PE1), Y1.3
unnamed: C101.1, C102.1, F101.1, R101.1, U101.4 (EN), U101.5 (VIN)
unnamed: C103.1, L101.1, U101.6 (SW)
unnamed: C103.2, U101.1 (CB)
unnamed: COUT101.1, COUT102.1, COUT103.1, L101.2, R103.1, R104.1
unnamed: D3.1 (K), R8.1
unnamed: D4.1 (K), R10.1
unnamed: D5.1 (K), R11.1
unnamed: D8.2 (A), R20.2
unnamed: D9.2 (A), R23.2
unnamed: D10.2 (A), R27.2
unnamed: D102.2 (A), R101.2
unnamed: D103.2 (A), R105.2
unnamed: IC1.8 ((PCINT0/MISO/PSCOUT2A)PB0), R_1.2
unnamed: IC1.9 ((PCINT1/MOSI/PSCOUT2B)PB1), R_2.2
unnamed 54: J2.13; also elsewhere on the board
unnamed 55: J2.16; also elsewhere on the board
unnamed: R6.2, R7.1, U1.4 (-)
unnamed: R16.2, R17.1, U3.4 (-)
unnamed: R102.1, R103.2, U101.3 (FB)
VCC: C1.2, C2.2, C4.1, C6.1, IC1.4 (VCC), J2.3, J2.6, J3.2, R1.1, R13.1, R22.1, R25.1, R29.1, R30.1, R31.1, R104.2, R105.1, U1.5 (V+), U3.5 (V+), U4.3 (VDD); also elsewhere on the board

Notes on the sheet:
Shutdown Sense Circuits
Throttle Sensor Circuits
Programming LED's
Drive Mode Sense Circuit
Power Flags
ATMega16M1
Gain: 1.45
Gain: 2
Input Capacitors
12V Indicator
Protection
BUCK CONVERTER
Feedback Divider
Inductor
Bootstrap Capacitor
Output Capacitors
VCC Jumper
5V Indicator
